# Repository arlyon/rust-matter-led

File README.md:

# matter-led

A Matter-compatible 5-channel RGBCW LED controller built on a custom PCB
with an ESP32-C6, written entirely in Rust. Pairs natively with Apple Home,
Google Home, and any other Matter controller -- no proprietary hub required.

## Hardware

### Board

The controller is a 2-layer PCB designed in KiCad 9. It accepts 24 V DC
input through a Molex 2601-1106 connector, protected by a 10 A mini blade
fuse (Littelfuse 0297010.WXNV). A Recom R-78E5.0-1.0 switching regulator
steps 24 V down to 5 V / 1 A to power the Waveshare ESP32-C6 module. Two
470 uF electrolytic capacitors (Panasonic EEUFR1V471L) filter the converter
input.

Five AO3400A N-channel MOSFETs in SOT-23 packages switch the LED channels
on the low side. Each gate is driven from a GPIO through a 100 ohm series
resistor; 10 kohm pull-downs hold the gates low during boot. The MOSFETs
switch the 24 V rail directly, so the LED strips see full supply voltage.

### LED strip

The board drives 24 V RGBCCT LED strips with a common-anode, 6-pin
configuration (V+, R, G, B, CW, WW). The target strip uses 5050-package
RGB LEDs alongside 2835-package tunable-white LEDs, with a colour
temperature range of 2000--6500 K and a CRI of 95. At 168 LEDs/m drawing
34.56 W/m, a 5 m reel pulls around 173 W. The strip is IP20 (no
weatherproofing). Five independent PWM channels allow continuous colour
temperature tuning between 2000 K and 6500 K, as well as full-gamut RGB
colour mixing.

An example strip that matches these specs:
https://www.aliexpress.com/item/1005006132338333.html

### Power supply

Use a 24 V DC supply rated for the strip length you intend to drive. The
board fuse is 10 A, so the practical ceiling is around 240 W at the input
connector. A Mean Well LRS-350-24 or equivalent is a reasonable choice for
a full 5 m strip.

### GPIO mapping

| GPIO | Channel    |
|------|------------|
| 1    | Red        |
| 0    | Green      |
| 10   | Blue       |
| 3    | Cold White |
| 2    | Warm White |
| 9    | BOOT (factory reset) |

## Firmware

The firmware is a `no_std` Rust binary targeting `riscv32imac-unknown-none-elf`.
It requires nightly Rust (minimum 1.88) for `type_alias_impl_trait` and
the alloc error handler.

### Architecture

The async runtime is [Embassy](https://embassy.dev). Hardware access goes
through `esp-hal`, and the Matter protocol stack is
[rs-matter](https://github.com/project-chip/rs-matter) with the
`rs-matter-embassy` integration layer. Networking uses `smoltcp` via
`embassy-net` with DHCPv4 and IPv6 support. BLE commissioning is handled
by `trouble-host` over the ESP32-C6's radio.

The device advertises as a Matter Extended Color Light (device type 0x10D)
on endpoint 1, exposing the following clusters:

- **OnOff** -- power state with smooth 400 ms transitions.
- **LevelControl** -- brightness from 1 to 254 (Matter range).
- **ColorControl** -- hue/saturation mode and colour temperature in mireds
  (153--500, i.e. 6500 K down to 2000 K).
- **Identify** -- cycles through red, green, blue to visually locate the
  device.

A second endpoint (endpoint 2) exposes an On/Off Light Switch that acts as
a "max brightness" override, driving all five channels at the current
brightness level simultaneously.

### PWM control

The LEDC peripheral is configured with a single 13-bit timer at 4882 Hz,
giving 8192 discrete duty levels per channel. A dedicated async task runs
at 50 Hz (20 ms per frame), interpolating between the current and target
PWM state with a cubic ease-in-out curve. RGB transitions are mixed in
Oklab colour space for perceptually uniform blending; CW/WW transitions
use linear interpolation in Kelvin space (converted from mireds). All
output values pass through gamma 2.2 correction before hitting the LEDC
registers.

### Colour temperature

The firmware maps the Matter mired range (153--500) to a mix ratio between
the CW and WW channels. Conversion goes through Kelvin
(`K = 1,000,000 / mireds`) and interpolates linearly in that space, which
is more perceptually uniform than interpolating in mireds directly.

### Memory layout

The ESP32-C6 has 8 MB of flash. The firmware reclaims bootloader RAM for
heap use:

| Region         | Size     | Purpose                             |
|----------------|----------|-------------------------------------|
| Heap           | 112 KB   | General allocations (peak ~72 KB)   |
| Bump allocator | 24 KB    | rs-matter internals (peak ~16 KB)   |
| Flash KV store | 128 KB   | Matter fabric and ACL persistence   |

The KV store sits at offset `0x700000` and uses `sequential-storage` with
32 x 4 KB sectors.

### Matter commissioning

The discriminator is derived from the last 12 bits of the device MAC
address, giving each board a unique but deterministic identity. The default
passcode is `20202021` (the Matter test value). Pairing data is printed to
the defmt log on boot.

To commission, use any Matter controller and enter the discriminator and
passcode, or generate a QR code with vendor ID `0xFFF1` and product ID
`0x8000`.

### Factory reset

Hold the BOOT button (GPIO 9) during power-on. The firmware erases the
128 KB flash KV store and reboots after a 2-second delay. All Matter
fabrics, ACLs, and saved state are wiped.

## Building

### Prerequisites

Install the toolchain via [mise](https://mise.jdx.dev):

```
mise install
```

This sets up nightly Rust with the `riscv32imac-unknown-none-elf` target
and the `espflash` tool.

Alternatively, install manually:

```
rustup toolchain install nightly
rustup target add riscv32imac-unknown-none-elf
cargo install espflash
```

### Compile and flash

```
cd firmware
cargo build --release
cargo espflash flash --release --monitor
```

The `--monitor` flag opens a serial console after flashing so you can see
defmt log output including the pairing discriminator.

## Hardware CI with KiBot

A GitHub Actions workflow runs [KiBot](https://github.com/INTI-CMNB/KiBot)
on every push or PR that touches schematic, PCB, or KiBot configuration
files. It uses the `ghcr.io/inti-cmnb/kicad9_auto_full` container image
and runs ERC/DRC preflight checks before generating outputs.

### Generated artifacts

All outputs land in `hardware/output/` and are uploaded as build artifacts.

| Directory    | Contents                                              |
|--------------|-------------------------------------------------------|
| `schematics` | Schematic PDF and SVG                                 |
| `gerbers`    | Gerber files (F/B Cu, SilkS, Mask, Paste, Edge.Cuts) + Excellon drill |
| `assembly`   | Pick-and-place CSV (JLC format, SMD only), full position file, interactive HTML BOM |
| `bom`        | JLC BOM (LCSC parts), Mouser/Digikey BOM (non-LCSC parts), Octopart 1-click import |
| `pcb`        | Top and bottom layer PDFs                             |
| `3d`         | STEP and VRML 3D models                               |

The BOM is split by sourcing. Components with an `LCSC` field go into the
JLC BOM for PCBA ordering; everything else (the ESP32-C6 module, Recom
regulator, fuse, connectors) goes into a separate BOM formatted for
Mouser/Digikey with MPN grouping. A third BOM variant is formatted for
[Octopart](https://octopart.com) one-click import -- upload the CSV and
Octopart resolves MPNs across distributors, shows stock and pricing, and
lets you build a cart in one step.

## Bill of materials

### On-board components

| Ref            | Part                   | Value / MPN         | Package    | LCSC    | Notes                          |
|----------------|------------------------|---------------------|------------|---------|--------------------------------|
| U1             | DC-DC converter        | R-78E5.0-1.0        | SIP-3      | --      | 24 V to 5 V, 1 A (Recom)      |
| U2             | MCU module             | ESP32-C6-Mini       | Castellated| --      | Waveshare, RISC-V 160 MHz, WiFi 6 + BLE 5 + Zigbee 3.0, 8 MB flash |
| Q1--Q5         | N-ch MOSFET            | AO3400A             | SOT-23     | --      | 30 V / 5.7 A, low-side LED switches |
| D1             | Schottky rectifier     | SS34                | SMC        | C211777 | 3 A / 40 V, reverse polarity protection |
| F1             | Fuse                   | 10 A                | Mini Blade | --      | Littelfuse 0297010.WXNV        |
| C1, C2         | Ceramic capacitor      | 100 nF              | 1206       | C13585  | Decoupling                     |
| C3             | Electrolytic capacitor | 470 uF 35 V         | Radial     | --      | EEUFR1V471L, regulator input   |
| R1,R3,R5,R7,R9 | Resistor              | 100 ohm             | 0402       | C25076  | MOSFET gate current limiting   |
| R2,R4,R6,R8,R10| Resistor              | 10 kohm             | 0402       | C25744  | MOSFET gate pull-down          |
| J1             | Power input connector  | Molex 2601-1106     | 2-pin      | --      | 24 V DC input                  |
| J2             | LED output connector   | XT30U-M             | XT30       | --      | RGBCW strip connection         |

### Off-board (not on PCB)

| Part              | Example                          | Notes                                    |
|-------------------|----------------------------------|------------------------------------------|
| 24 V power supply | Mean Well LRS-350-24             | Size to strip length; fuse limits 240 W  |
| RGBCCT LED strip  | 5050 RGB + 2835 CCT, 24 V, IP20 | 2000--6500 K, CRI 95, 168 LEDs/m, 34.56 W/m, 6-pin |

The KiBot CI generates three BOM formats automatically: a JLC-formatted
CSV for LCSC parts (ready for JLCPCB PCBA upload), a Mouser/Digikey BOM
grouped by MPN for manual ordering, and an Octopart CSV for one-click
quoting across distributors. All three are available as build artifacts
under `hardware/output/bom/`.

## Project structure

```
.
├── firmware/           Rust firmware for the ESP32-C6
│   ├── src/bin/        Entry point (main.rs)
│   ├── src/clusters/   Matter cluster handlers (OnOff, LevelControl, ColorControl, Identify)
│   ├── src/led/        PWM control, colour conversion, device state
│   └── tests/          On-target embedded tests
├── hardware/           KiCad 9 schematic and PCB
│   ├── external/       Third-party symbol libraries
│   └── internal/       Custom symbols (Waveshare module)
├── crates/
│   └── sticky-signal/  Async signal primitive (no_std, multi-waiter)
├── config.kibot.yaml   KiBot output definitions
└── .github/workflows/  CI for hardware artifact generation
```

## License

See individual crate and hardware directories for licensing details.

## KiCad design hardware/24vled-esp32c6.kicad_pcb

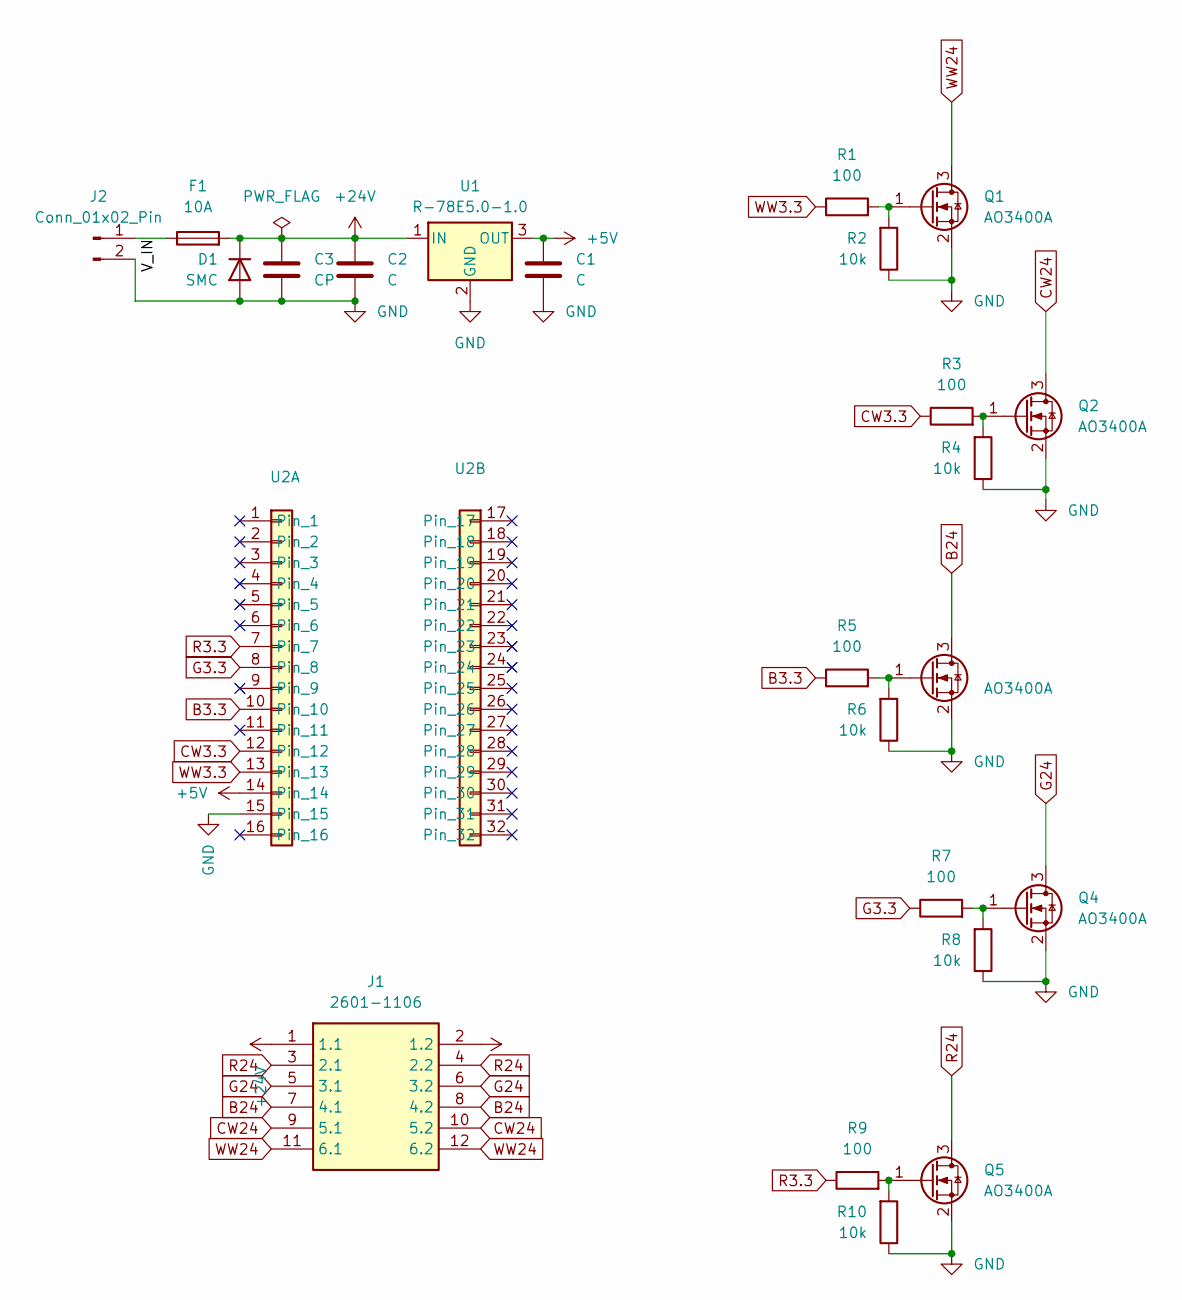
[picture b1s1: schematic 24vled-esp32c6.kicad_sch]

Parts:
C1, C2: C; C_1206_3216Metric; LCSC C13585
C3: CP; CP_Radial_D8.0mm_P3.50mm
D1: SMC; D_SMC; LCSC C211777
F1: 10A; Fuse_Blade_Mini_directSolder
J1: 2601-1106; 26011106; Manufacturer_Part_Number 2601-1106
J2: Conn_01x02_Pin; AMASS_XT30U-M_1x02_P5.0mm_Vertical
Q1, Q2, Q3, Q4, Q5: AO3400A; SOT-23
R1, R3, R5, R7, R9: 100; R_0402_1005Metric; LCSC C25076
R2, R4, R6, R8, R10: 10k; R_0402_1005Metric; LCSC C25744
U1: R-78E5.0-1.0; Converter_DCDC_RECOM_R-78E-0.5_THT
U2: Waveshare ESP32c6

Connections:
+5V: C1.1, U1.3 (OUT), U2.14
+24V: C2.1, C3.1, D1.1 (K), F1.2, J1.1 (1.1), J1.2 (1.2), U1.1 (IN)
/V_IN: F1.1, J2.1
B3.3: R5.1, U2.10
B24: J1.7 (4.1), J1.8 (4.2), Q3.3 (D)
CW3.3: R3.1, U2.12
CW24: J1.9 (5.1), J1.10 (5.2), Q2.3 (D)
G3.3: R7.1, U2.8
G24: J1.5 (3.1), J1.6 (3.2), Q4.3 (D)
GND: C1.2, C2.2, C3.2, D1.2 (A), J2.2, Q1.2 (S), Q2.2 (S), Q3.2 (S), Q4.2 (S), Q5.2 (S), R2.1, R4.1, R6.1, R8.1, R10.1, U1.2 (GND), U2.15
unnamed: Q1.1 (G), R1.2, R2.2
unnamed: Q2.1 (G), R3.2, R4.2
unnamed: Q3.1 (G), R5.2, R6.2
unnamed: Q4.1 (G), R7.2, R8.2
unnamed: Q5.1 (G), R9.2, R10.2
R3.3: R9.1, U2.7
R24: J1.3 (2.1), J1.4 (2.2), Q5.3 (D)
WW3.3: R1.1, U2.13
WW24: J1.11 (6.1), J1.12 (6.2), Q1.3 (D)

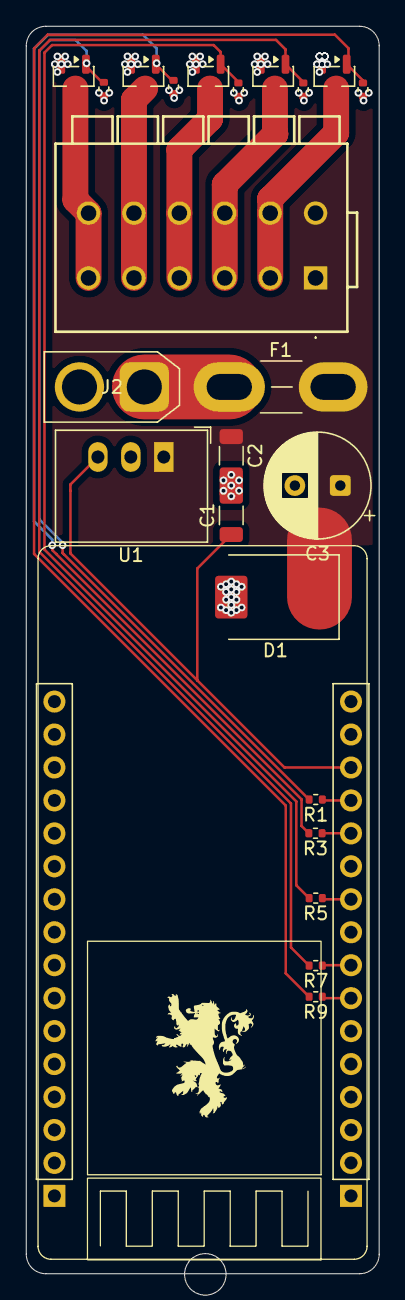
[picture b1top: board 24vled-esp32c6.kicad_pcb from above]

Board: 2 copper layers, 27.2 x 96.1 mm, 24 parts (0 on the bottom side), 19 nets.

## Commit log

2025-10-24 Added raw files for cleaning and project setup
2025-10-24 move to hw folder
2025-10-24 add esp32c6 template
2025-10-24 checkpoint
2025-10-24 firmware
2025-10-26 hardware v1
2025-10-27 hardware v2
2025-10-27 its working!!!
2025-10-31 add lib loader and bump deps
2025-10-31 move code into lib
2025-11-01 more refactor, get matter pair working
2025-11-05 add kibot
2025-11-05 fix schematic warnings and kibot
2025-11-05 fix all pcb warnings and use larger resistors
2025-11-05 dont use separate files
2025-11-05 update pages
2025-11-05 jlc formatting for bom and pick-n-place
2026-02-15 add the large cap and remove the flyback diodes
2026-02-15 final version!
2026-02-15 fix warnings and add part numbers
2026-02-15 update part number
2026-02-15 add some more part numbers
2026-02-15 change to 3.5mm file
2026-02-15 add m.2 style cutout
2026-02-15 ignore edge cut violation
2026-02-15 replace with npth for financial reasons
2026-02-16 get rid of copper
2026-02-16 add octopart bom generation
2026-02-16 remove check
2026-02-16 fix filters
2026-02-16 fix columns
2026-02-16 add bom parts
2026-02-16 some kibot fixes
2026-02-16 add fuse and fix filtering
2026-02-17 impl full matter commissioning for basic light
2026-02-17 working!
2026-02-17 get a handle on memory usage
2026-02-17 update embassy deps
2026-02-17 add additional declarations and stub impls
2026-02-18 some more impl
2026-03-10 stable pairing code
2026-03-11 integrate basic (broken) PWM
2026-03-11 switch to LEDC
2026-03-11 identify command
2026-03-11 fix broken timers
2026-03-11 impl CCCW RGB + brightness control
2026-03-11 perceptual lerp
2026-03-11 stub out more settings and improve the hsv / temp calculations
2026-03-11 MAX BRIGHTNESS mode and some ergonomics
    - 13 bit duty + 4.8khz
    - on/off fading animations
    - gamma correction
    - oklab color space
2026-05-13 add readme
